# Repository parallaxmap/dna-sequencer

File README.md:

# DNA Sequencer

A flexible MIDI sequencer powered by a Raspberry Pi Pico 2 (RP2350), inspired by sequencers found in the Korg Volca and Elektron boxes. Aims to be accessible, affordable, repurposable, and expandable.

## Current features
- RPi Pico 2 microcontroller, the brains of the sequencer
- MIDI output via 3.5mm TRS, or USB
- 16 keys for step editing, note input, or other custom macros
- 6 keys for navigation (get ready to menu dive!)
- 8 incremental encoders for CC/parameter adjustment and macros
- 128x64 1.3" OLED display
- All components are through-hole for easy soldering, and readily available

## Planned features
- 8 polyphonic tracks with different modes to facilitate various types of sequencing (e.g drum, chord, arp, euclidian, etc etc), can be assigned to any 16 MIDI channels
- 64 step sequencer with the ability to sequence 8 CC parameters, variable length, microtiming, and randomization/generation features
- 16 patterns with chaining

## Why'd you make this?
Currently the options for standalone hardware MIDI sequencers are either budget sequencers that do not have a vast featureset and, at least to myself, were limiting in terms of potential creativity, or more feature rich sequencers which cost a couple arms and legs. I wanted to make a device that would help bridge the gap between those two mountains and leverage the power of DIY & open source in order to create an accessible, affordable, repurposable, and expandable hardware sequencer. Additionally, this project serves as my first 100% serious hardware project, so all of the processes I learn throughout the journey of creating this device will be invaluable to me and whatever future endeavours lie before me... learning is fun!

## Images/Videos
PCB

Schematic

## Bill of Materials

Choice of keycaps is up to you, as long as they're compatible with Cherry MX. You will also need a Micro USB cable for power and USB MIDI, and a 3.5 TRS to DIN converter for regular MIDI

|Item                   |Description                  |Quantity|Unit Price ($)|Total Price ($)|URL                                                  |Total |
|-----------------------|-----------------------------|--------|--------------|---------------|-----------------------------------------------------|------|
|MBB02070C1009FCT00     |10 Ohm resistor              |5       |$0.1346       |$0.6730        |https://www.lcsc.com/product-detail/C1364448.html    |$0.6730|
|MBB02070C3309FCT00     |33 Ohm resistor              |5       |$0.0748       |$0.3740        |https://www.lcsc.com/product-detail/C1366513.html    |$1.05 |
|MCP23017-E/SP          |I/O expander (I2C)           |1       |$2.8158       |$2.8158        |https://www.lcsc.com/product-detail/C4992459.html    |$3.86 |
|PEC12R-4120F-S0012     |Rotary encoder               |8       |$1.8791       |$15.0328       |https://www.lcsc.com/product-detail/C143801.html     |$18.90|
|SJ1-3533NG             |3.5mm TRS jack               |1       |$1.6565       |$1.6565        |https://www.lcsc.com/product-detail/C4992459.html    |$20.55|
|KH-2.54FH-1X20P-H8.5   |Socket (20 pins)             |5       |$0.1722       |$0.8610        |https://www.lcsc.com/product-detail/C2905423.html    |$21.41|
| PH2.54-1X20P-H25      |Header (20 pins)             |5       |$0.0488       |$0.2440        |https://www.lcsc.com/product-detail/C42431804.html   |$21.66|
|IC-28P                 |DIP socket                   |17      |$0.0510       |$0.8670        |https://www.lcsc.com/product-detail/C5289491.html    |$22.52|
|M3x10+6Cu              |Standoffs                    |10      |$0.0387       |$0.3870        |https://www.lcsc.com/product-detail/C551322.html     |$22.91|
|hexagon NUT M3         |Hex nut                      |100     |$0.0017       |$0.1700        |https://www.lcsc.com/product-detail/C133377.html     |$23.08|
|1N4148                 |Diodes                       |50      |$0.0116       |$0.5800        |https://www.lcsc.com/product-detail/C402212.html     |$23.66|
|SH1106                 |OLED display module          |1       |$3.6800       |$3.6800        |https://www.aliexpress.com/item/1005006072386746.html|$27.34|
|MIDI DIN to 3.5mm TRS  |DIN/TRS converter cable      |1       |$8.2000       |$8.2000        |https://www.aliexpress.com/item/1005009365055437.html|$35.54|
|Ugreen Micro USB Cable |Micro USB for microcontroller|1       |$2.6900       |$2.6900        |https://www.aliexpress.com/item/32391749504.html     |$38.23|
|XDA Profile PBT Keycaps|1U keycaps (30pcs)           |1       |$5.4100       |$5.4100        |https://www.aliexpress.com/item/1005005514406952.html|$43.64|
|11mm Potentiometer Knob|Knobs for encoders (10pcs)   |1       |$2.1000       |$2.1000        |https://www.aliexpress.com/item/1005003991686731.html|$45.74|
|Gateron Switches KS9   |Key switch (30pcs)           |1       |$12.9500      |$12.9500       |https://www.aliexpress.com/item/1005007474127225.html|$58.69|
|RPI Pico 2             |Microcontroller              |1       |$8.9800       |$8.9800        |https://www.aliexpress.com/item/1005008201547951.html|$67.67|
|JLCPCB                 |PCB x 5 and shipping costs   |1       |$24.42        |$24.42         |                                                     |$92.09|
|LCSC                   |LCSC shipping costs          |1       |$8.84         |$8.84          |                                                     |$100.93|

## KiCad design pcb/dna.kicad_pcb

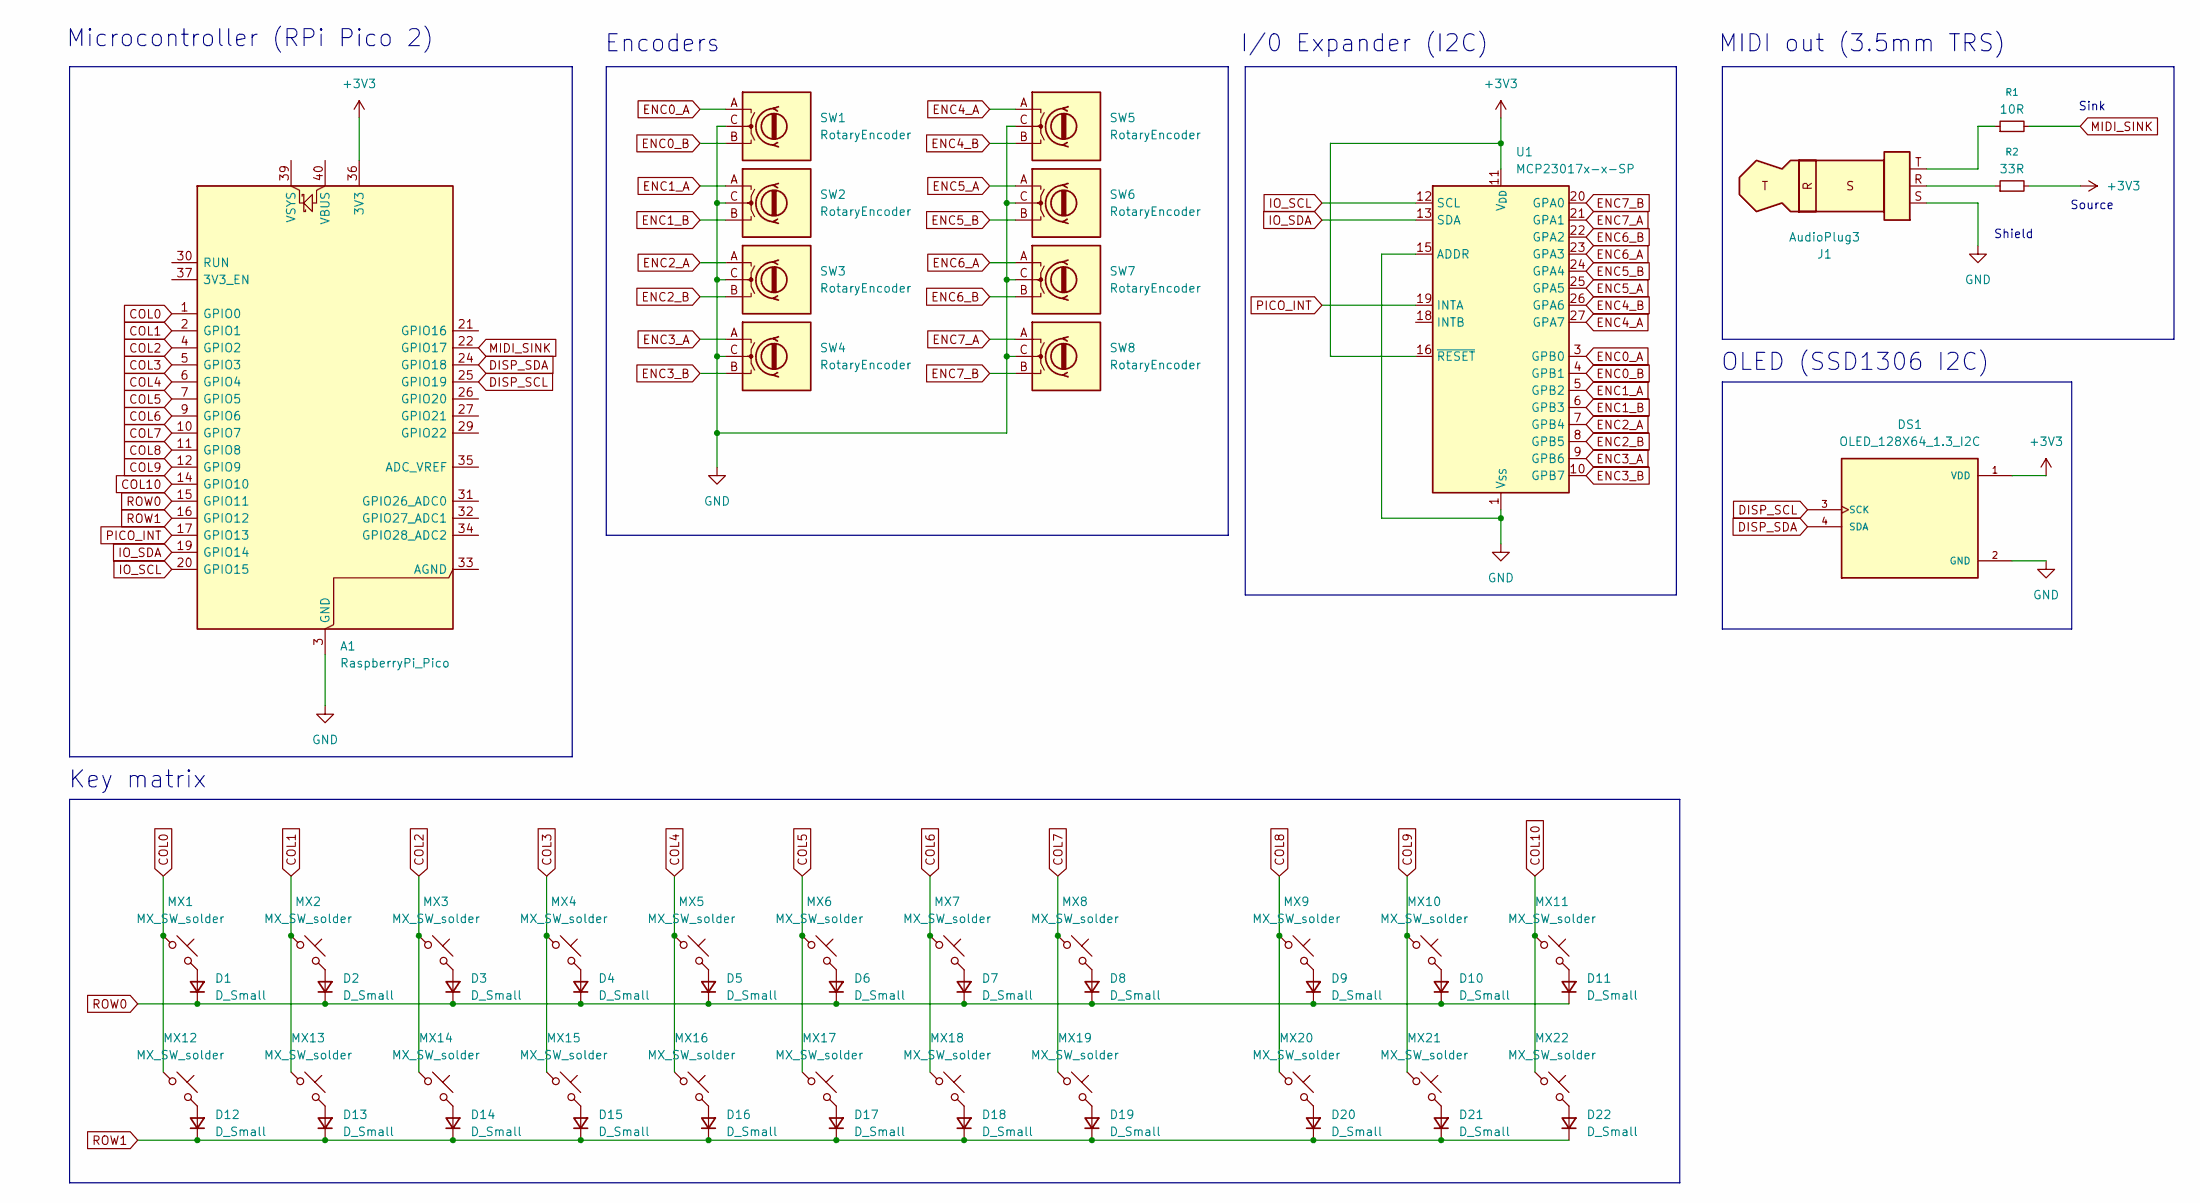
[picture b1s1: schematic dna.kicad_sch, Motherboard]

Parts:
A1: RaspberryPi_Pico; RaspberryPi_Pico_Common_THT
D1, D2, D3, D4, D5, D6, D7, D8, D9, D10, D11, D12, D13, D14, D15, D16, D17, D18, D19, D20, D21, D22: D_Small; D_DO-35_SOD27_P7.62mm_Horizontal
DS1: OLED_128X64_1.3_I2C; LCD_OLED_128X64_1.3_I2C; PARTREV NA
J1: AudioPlug3; Jack_3.5mm_CUI_SJ1-3533NG_Horizontal_CircularHoles
MX1, MX2, MX3, MX4, MX5, MX6, MX7, MX8, MX9, MX10, MX11, MX12, MX13, MX14, MX15, MX16, MX17, MX18, MX19, MX20, MX21, MX22: MX_SW_solder; SW_Cherry_MX_PCB_1.00u
R1: 10R; R_Axial_DIN0207_L6.3mm_D2.5mm_P7.62mm_Horizontal
R2: 33R; R_Axial_DIN0207_L6.3mm_D2.5mm_P7.62mm_Horizontal
SW1, SW2, SW3, SW4, SW5, SW6, SW7, SW8: RotaryEncoder; RotaryEncoder_Bourns_Vertical_PEC12R-3x17F-Sxxxx
U1: MCP23017x-x-SP; DIP-28_W7.62mm

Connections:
+3V3: A1.36 (3V3), DS1.1 (VDD), R2.2, U1.11 (V_{DD}), U1.16 (~RESET)
COL0: A1.1 (GPIO0), MX1.1, MX12.1
COL1: A1.2 (GPIO1), MX2.1, MX13.1
COL2: A1.4 (GPIO2), MX3.1, MX14.1
COL3: A1.5 (GPIO3), MX4.1, MX15.1
COL4: A1.6 (GPIO4), MX5.1, MX16.1
COL5: A1.7 (GPIO5), MX6.1, MX17.1
COL6: A1.9 (GPIO6), MX7.1, MX18.1
COL7: A1.10 (GPIO7), MX8.1, MX19.1
COL8: A1.11 (GPIO8), MX9.1, MX20.1
COL9: A1.12 (GPIO9), MX10.1, MX21.1
COL10: A1.14 (GPIO10), MX11.1, MX22.1
DISP_SCL: A1.25 (GPIO19), DS1.3 (SCK)
DISP_SDA: A1.24 (GPIO18), DS1.4 (SDA)
ENC0_A: SW1.A, U1.3 (GPB0)
ENC0_B: SW1.B, U1.4 (GPB1)
ENC1_A: SW2.A, U1.5 (GPB2)
ENC1_B: SW2.B, U1.6 (GPB3)
ENC2_A: SW3.A, U1.7 (GPB4)
ENC2_B: SW3.B, U1.8 (GPB5)
ENC3_A: SW4.A, U1.9 (GPB6)
ENC3_B: SW4.B, U1.10 (GPB7)
ENC4_A: SW5.A, U1.27 (GPA7)
ENC4_B: SW5.B, U1.26 (GPA6)
ENC5_A: SW6.A, U1.25 (GPA5)
ENC5_B: SW6.B, U1.24 (GPA4)
ENC6_A: SW7.A, U1.23 (GPA3)
ENC6_B: SW7.B, U1.22 (GPA2)
ENC7_A: SW8.A, U1.21 (GPA1)
ENC7_B: SW8.B, U1.20 (GPA0)
GND: A1.3 (GND), A1.8 (GND), A1.13 (GND), A1.18 (GND), A1.23 (GND), A1.28 (GND), A1.38 (GND), DS1.2 (GND), J1.S, SW1.C, SW2.C, SW3.C, SW4.C, SW5.C, SW6.C, SW7.C, SW8.C, U1.1 (V_{SS}), U1.15 (ADDR)
IO_SCL: A1.20 (GPIO15), U1.12 (SCL)
IO_SDA: A1.19 (GPIO14), U1.13 (SDA)
MIDI_SINK: A1.22 (GPIO17), R1.2
unnamed: D1.2 (A), MX1.2
unnamed: D2.2 (A), MX2.2
unnamed: D3.2 (A), MX3.2
unnamed: D4.2 (A), MX4.2
unnamed: D5.2 (A), MX5.2
unnamed: D6.2 (A), MX6.2
unnamed: D7.2 (A), MX7.2
unnamed: D8.2 (A), MX8.2
unnamed: D9.2 (A), MX9.2
unnamed: D10.2 (A), MX10.2
unnamed: D11.2 (A), MX11.2
unnamed: D12.2 (A), MX12.2
unnamed: D13.2 (A), MX13.2
unnamed: D14.2 (A), MX14.2
unnamed: D15.2 (A), MX15.2
unnamed: D16.2 (A), MX16.2
unnamed: D17.2 (A), MX17.2
unnamed: D18.2 (A), MX18.2
unnamed: D19.2 (A), MX19.2
unnamed: D20.2 (A), MX20.2
unnamed: D21.2 (A), MX21.2
unnamed: D22.2 (A), MX22.2
unnamed: J1.R, R2.1
unnamed: J1.T, R1.1
PICO_INT: A1.17 (GPIO13), U1.19 (INTA)
ROW0: A1.15 (GPIO11), D1.1 (K), D2.1 (K), D3.1 (K), D4.1 (K), D5.1 (K), D6.1 (K), D7.1 (K), D8.1 (K), D9.1 (K), D10.1 (K), D11.1 (K)
ROW1: A1.16 (GPIO12), D12.1 (K), D13.1 (K), D14.1 (K), D15.1 (K), D16.1 (K), D17.1 (K), D18.1 (K), D19.1 (K), D20.1 (K), D21.1 (K), D22.1 (K)

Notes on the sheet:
Key matrix
Sink
I/0 Expander (I2C)
Source
Microcontroller (RPi Pico 2)
MIDI out (3.5mm TRS)
OLED (SSD1306 I2C)
Encoders
Shield

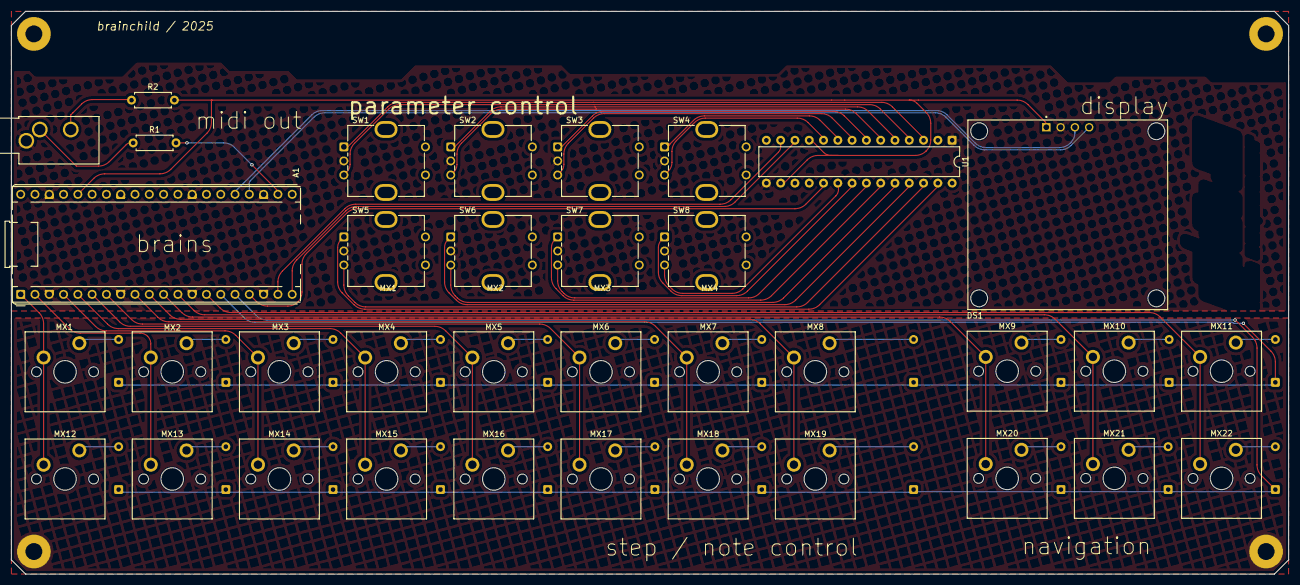
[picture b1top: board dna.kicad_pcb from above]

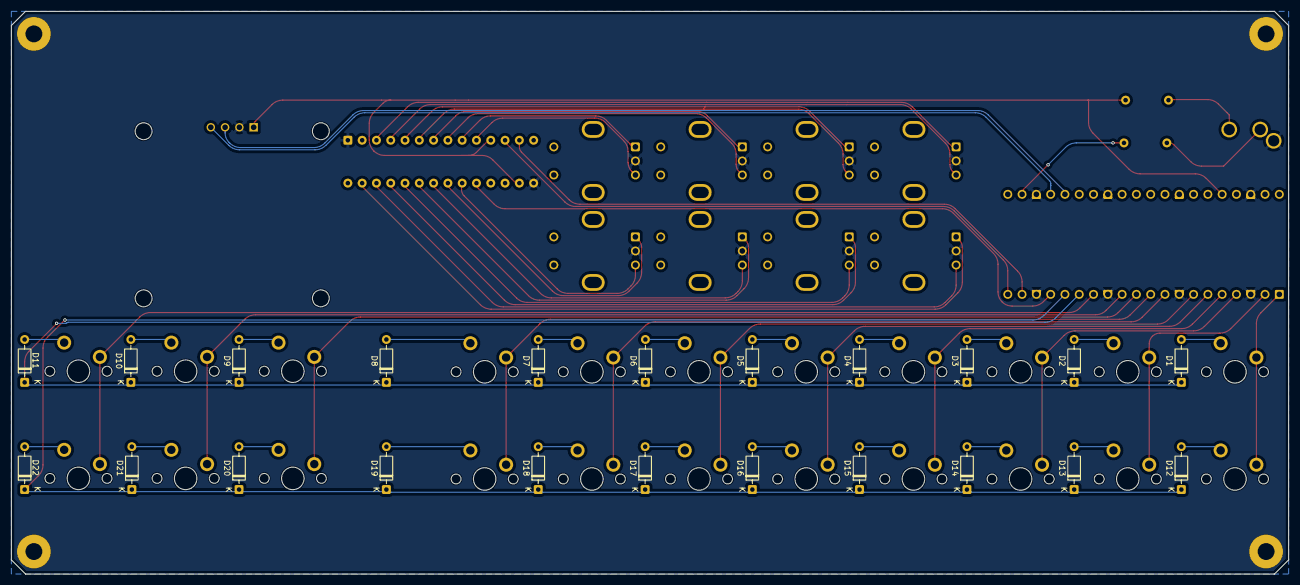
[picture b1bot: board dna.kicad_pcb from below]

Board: 2 copper layers, 227.0 x 100.0 mm, 58 parts (22 on the bottom side), 61 nets.

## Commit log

2025-10-31 Add KiCad source files
2025-11-01 Update PCB source files
2025-11-01 Add BOM
